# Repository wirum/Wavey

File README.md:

Projeto em dev incial, nada pra ver aqui.. AINDA!

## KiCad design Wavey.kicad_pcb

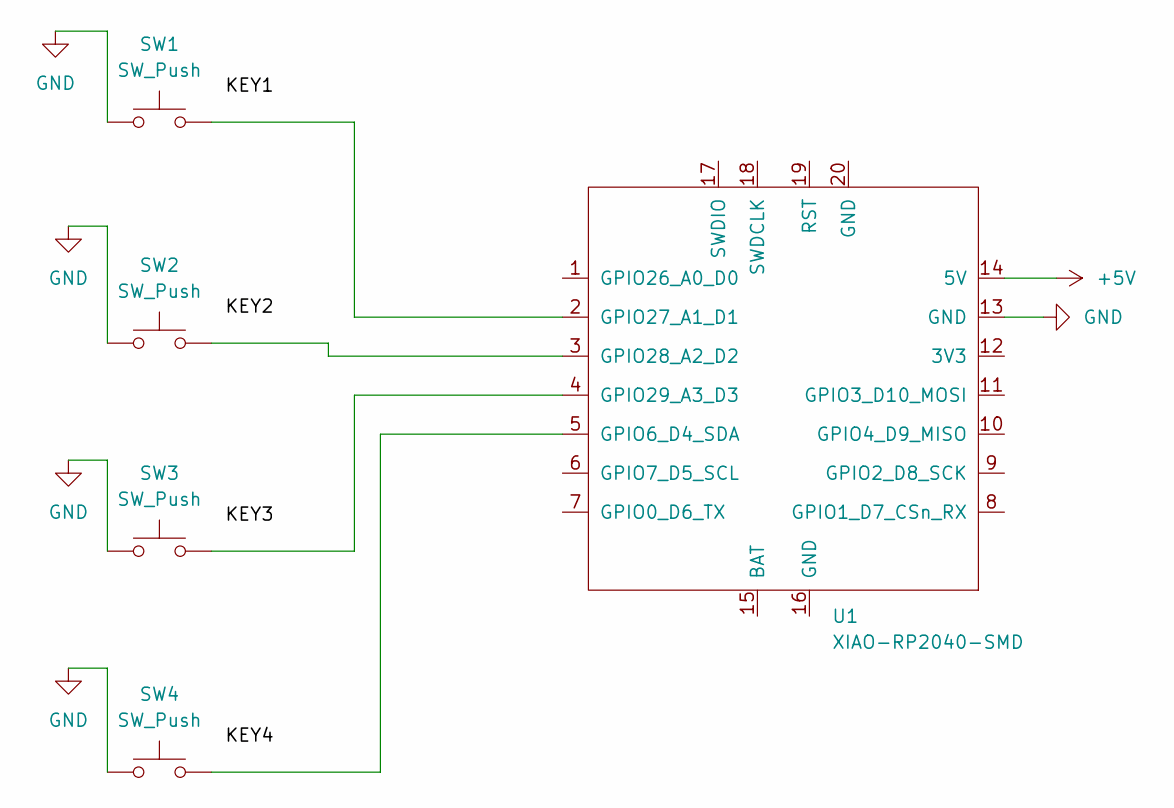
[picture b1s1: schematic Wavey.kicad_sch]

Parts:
SW1, SW2, SW3, SW4: SW_Push; SW_Cherry_MX_1.00u_PCB
U1: XIAO-RP2040-SMD

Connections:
+5V: U1.14 (5V)
GND: SW1.1, SW2.1, SW3.1, SW4.1, U1.13 (GND)
unnamed: SW4.2, U1.5 (GPIO6_D4_SDA)
unnamed: SW1.2, U1.2 (GPIO27_A1_D1)
unnamed: SW2.2, U1.3 (GPIO28_A2_D2)
unnamed: SW3.2, U1.4 (GPIO29_A3_D3)

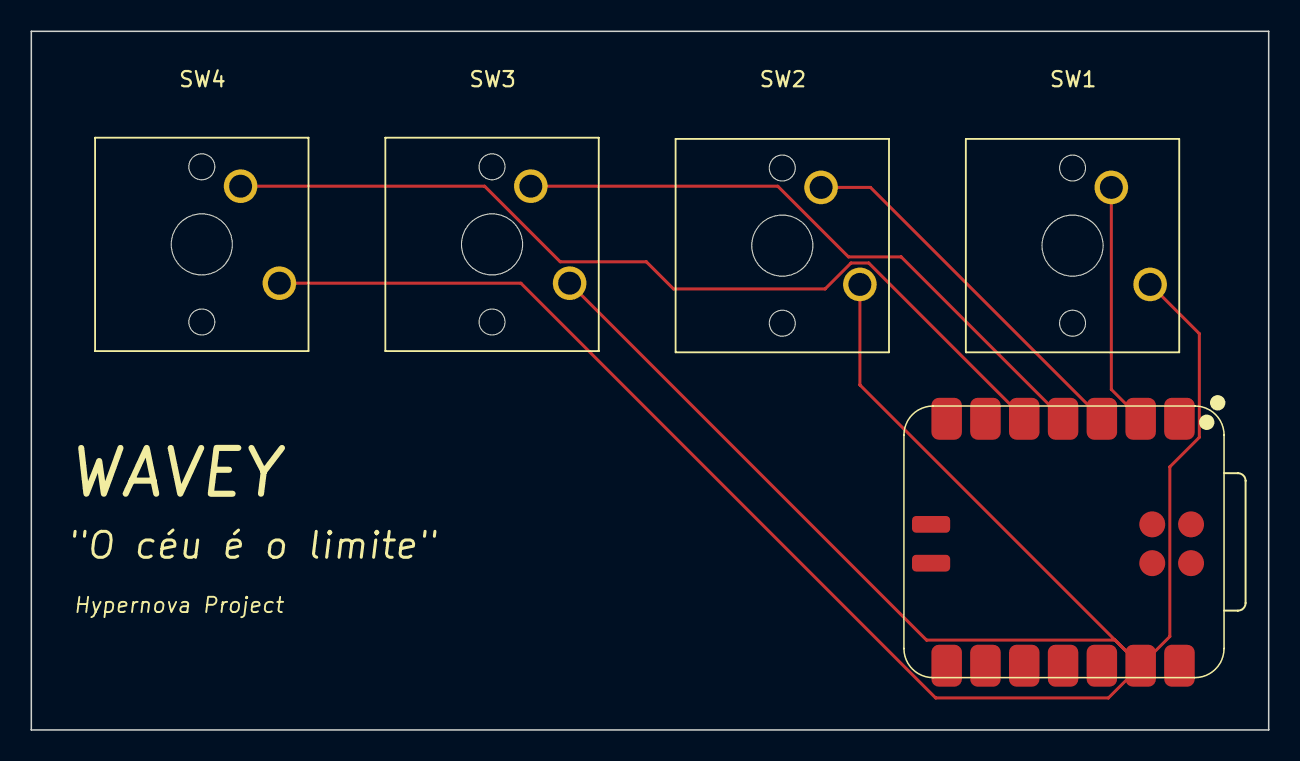
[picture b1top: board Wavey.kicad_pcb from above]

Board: 2 copper layers, 81.0 x 45.7 mm, 5 parts (0 on the bottom side), 5 nets.

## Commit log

2026-01-10 Add initial project description to README
